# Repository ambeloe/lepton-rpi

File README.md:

# lepton-rpi

# dimensions are now fine, but it still shouldnt work

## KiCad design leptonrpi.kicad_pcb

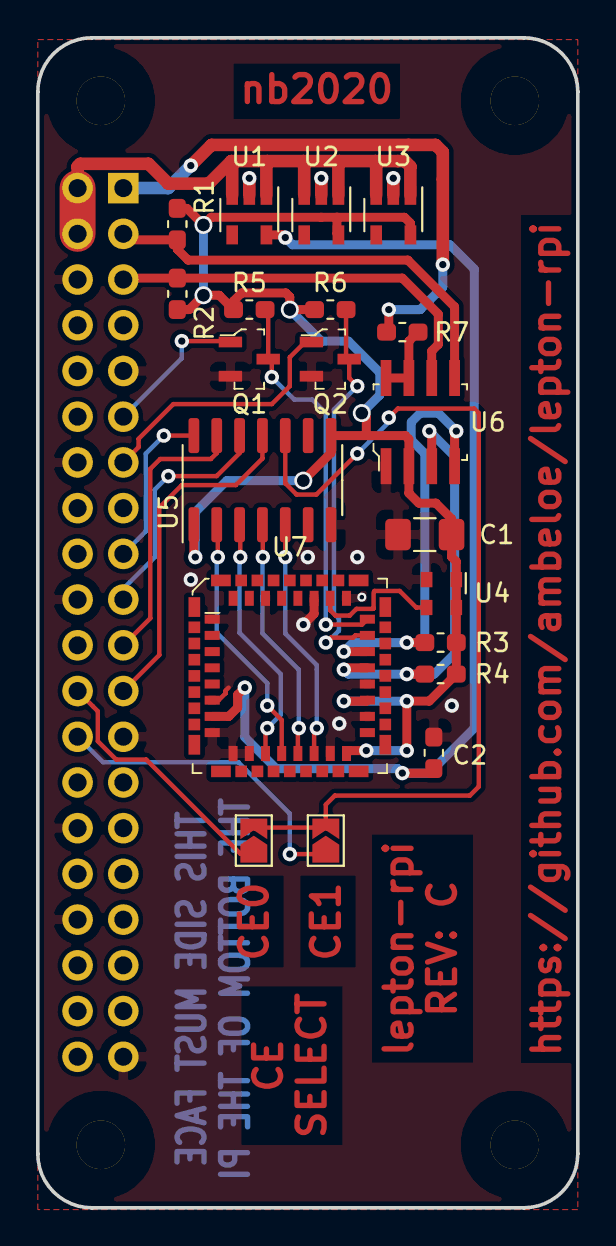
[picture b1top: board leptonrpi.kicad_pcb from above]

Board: 2 copper layers, 30.0 x 65.0 mm, 21 parts (1 on the bottom side), 24 nets.

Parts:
C1: 100uF; C_1206_3216Metric_Pad1.42x1.75mm_HandSolder
C2: 10uF; C_0603_1608Metric_Pad1.05x0.95mm_HandSolder
J1: Raspberry_Pi_2_3; rpogi2
JP1, JP2: SolderJumper_2_Open; SolderJumper-2_P1.3mm_Open_TrianglePad1.0x1.5mm
Q1, Q2: BSS84; SOT-23-3
R1, R2, R3, R4: 22k; R_0603_1608Metric_Pad1.05x0.95mm_HandSolder
R5, R6: 10k; R_0603_1608Metric_Pad1.05x0.95mm_HandSolder
R7: 200k; R_0603_1608Metric_Pad1.05x0.95mm_HandSolder
U1: TLV73312PDBV; SOT-23-5
U2, U3: TLV73328PDBV; SOT-23-5
U4: ASDMB-xxxMHz; Oscillator_SMD_Abracon_ASDMB-4Pin_2.5x2.0mm
U5: TXB0104D; SOIC-14_3.9x8.7mm_P1.27mm
U6: PCA9306D_118; SOIC-8_W3.9mm
U7: Flir_LEPTON; FLIR_Lepton_Socket_1050281001

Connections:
+1V2: C2.1, U1.5, U7.7
+2V8: C1.1, R3.1, R4.1, R5.1, R6.1, U2.5, U3.5, U4.1, U4.4, U5.1, U5.8, U6.2, U7.16, U7.19
+3V3: J1.1, J1.17, R1.1, R2.1, R7.1, U5.14
+5V: J1.2, J1.4, U1.1, U1.3, U2.1, U2.3, U3.1, U3.3
/CS: JP1.2, JP2.2, U5.10
/L_CS: U5.5, U7.14
/L_MISO: U5.2, U7.12
/L_MOSI: U5.3, U7.11
/L_SCLK: U5.4, U7.13
/MISO: J1.21, U5.13
/MOSI: J1.19, U5.12
CLK: J1.23, U4.3, U5.11, U7.26
GND: C1.2, C2.2, J1.6, J1.9, J1.14, J1.20, J1.25, J1.30, J1.34, J1.39, Q1.2, Q2.2, U1.2, U2.2, U3.2, U4.2, U5.7, U6.1, U7.1, U7.6, U7.8, U7.9, U7.10, U7.15, U7.18, U7.20, U7.25, U7.27, U7.30
HSCL0: J1.5, R2.2, U6.6
HSDA0: J1.3, R1.2, U6.5
LSCL0: R4.2, U6.3, U7.21
LSDA0: R3.2, U6.4, U7.22
unnamed: J1.11, Q1.1
unnamed: J1.13, Q2.1
unnamed: J1.24, JP2.1
unnamed: J1.26, JP1.1
unnamed: R7.2, U6.7, U6.8
PW_DN: Q2.3, R6.2, U7.23
RESET: Q1.3, R5.2, U7.24

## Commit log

2020-09-07 rev a
    removed all the vias that were in pads
    added labels
    added fun
2020-09-07 REV: A final
2020-09-27 fixed width
2020-10-25 added pdf schematic for convenience
2021-02-06 should have fixed the i2c bus being reversed
    rev c
